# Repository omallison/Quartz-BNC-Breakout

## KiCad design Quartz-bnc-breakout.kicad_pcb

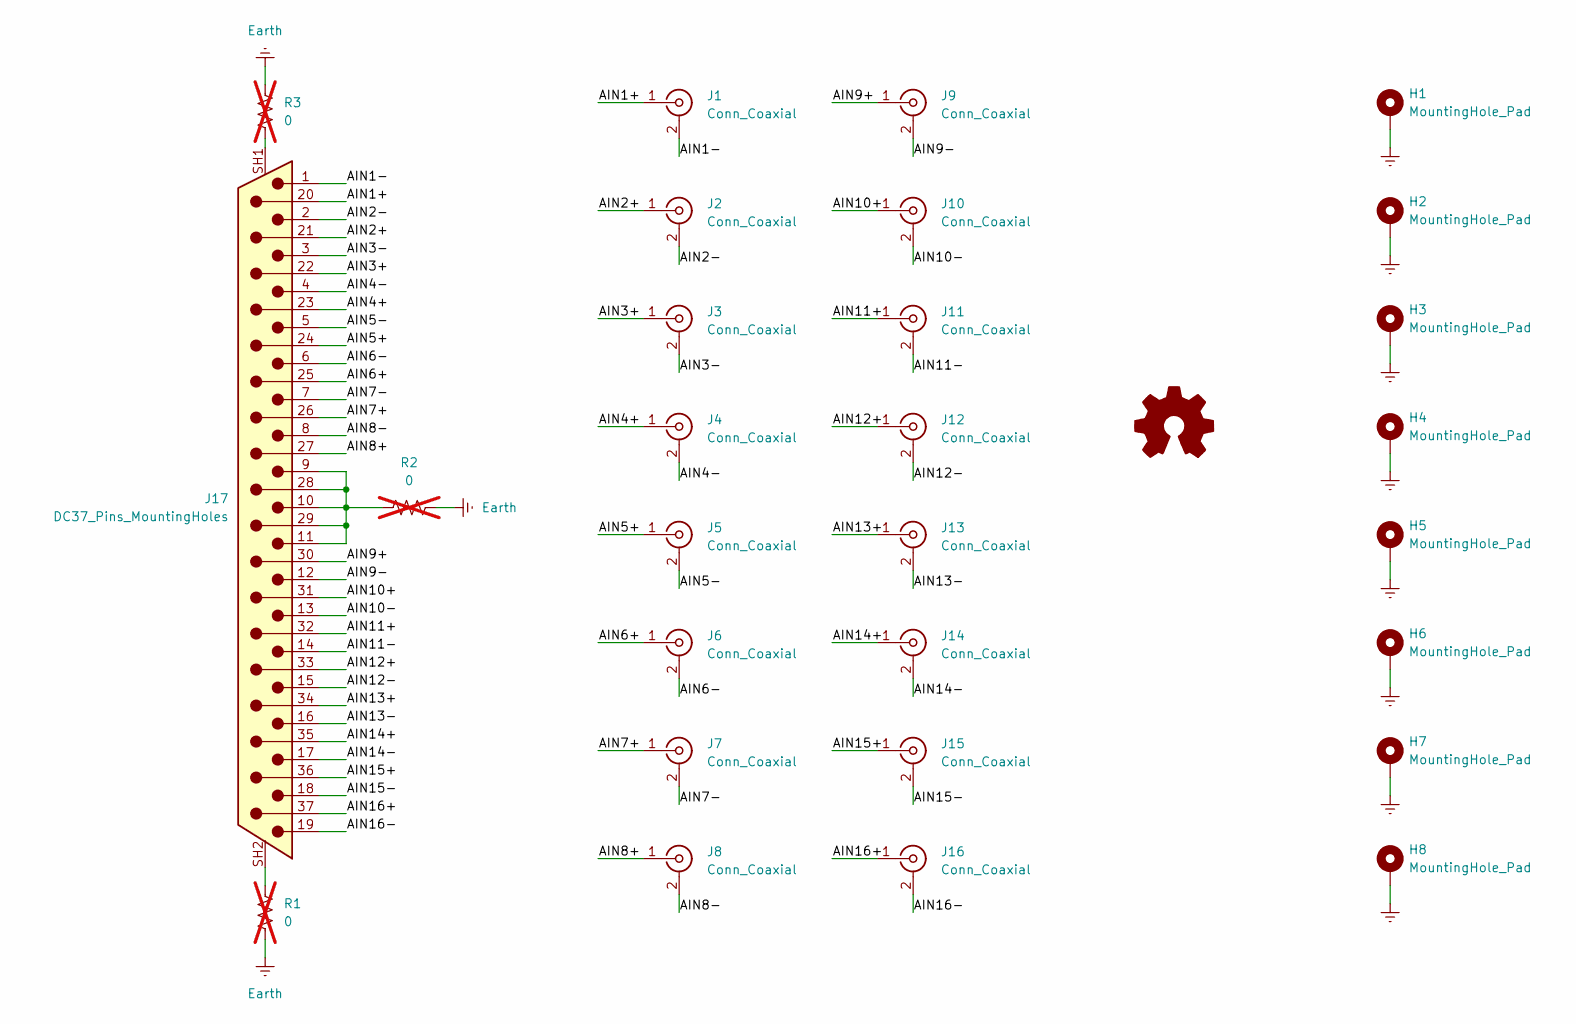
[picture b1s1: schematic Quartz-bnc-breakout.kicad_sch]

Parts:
H1, H2, H3, H4, H5, H6, H7, H8: MountingHole_Pad; MountingHole_3.4mm_Pad
J1, J2, J3, J4, J5, J6, J7, J8, J9, J10, J11, J12, J13, J14, J15, J16: Conn_Coaxial; BNC_Amphenol_031-5539_Vertical; MPN 5227222-2
J17: DC37_Pins_MountingHoles; DSUB-37_Pins_Vertical_P2.77x2.84mm_MountingHoles; MPN 5787686-1
Logo1: Logo_Open_Hardware_Small; Logo_2X
R1, R2, R3: 0; R_0805_2012Metric; not fitted

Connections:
/AIN1+: J1.1 (In), J17.20
/AIN1-: J1.2 (Ext), J17.1
/AIN2+: J2.1 (In), J17.21
/AIN2-: J2.2 (Ext), J17.2
/AIN3+: J3.1 (In), J17.22
/AIN3-: J3.2 (Ext), J17.3
/AIN4+: J4.1 (In), J17.23
/AIN4-: J4.2 (Ext), J17.4
/AIN5+: J5.1 (In), J17.24
/AIN5-: J5.2 (Ext), J17.5
/AIN6+: J6.1 (In), J17.25
/AIN6-: J6.2 (Ext), J17.6
/AIN7+: J7.1 (In), J17.26
/AIN7-: J7.2 (Ext), J17.7
/AIN8+: J8.1 (In), J17.27
/AIN8-: J8.2 (Ext), J17.8
/AIN9+: J9.1 (In), J17.30
/AIN9-: J9.2 (Ext), J17.12
/AIN10+: J10.1 (In), J17.31
/AIN10-: J10.2 (Ext), J17.13
/AIN11+: J11.1 (In), J17.32
/AIN11-: J11.2 (Ext), J17.14
/AIN12+: J12.1 (In), J17.33
/AIN12-: J12.2 (Ext), J17.15
/AIN13+: J13.1 (In), J17.34
/AIN13-: J13.2 (Ext), J17.16
/AIN14+: J14.1 (In), J17.35
/AIN14-: J14.2 (Ext), J17.17
/AIN15+: J15.1 (In), J17.36
/AIN15-: J15.2 (Ext), J17.18
/AIN16+: J16.1 (In), J17.37
/AIN16-: J16.2 (Ext), J17.19
Earth: H1.1, H2.1, H3.1, H4.1, H5.1, H6.1, H7.1, H8.1, R1.2, R2.2, R3.1
unnamed: J17.SH1 (PAD), R3.2
unnamed: J17.SH2 (PAD), R1.1
unnamed: J17.9, J17.10, J17.11, J17.28, J17.29, R2.1

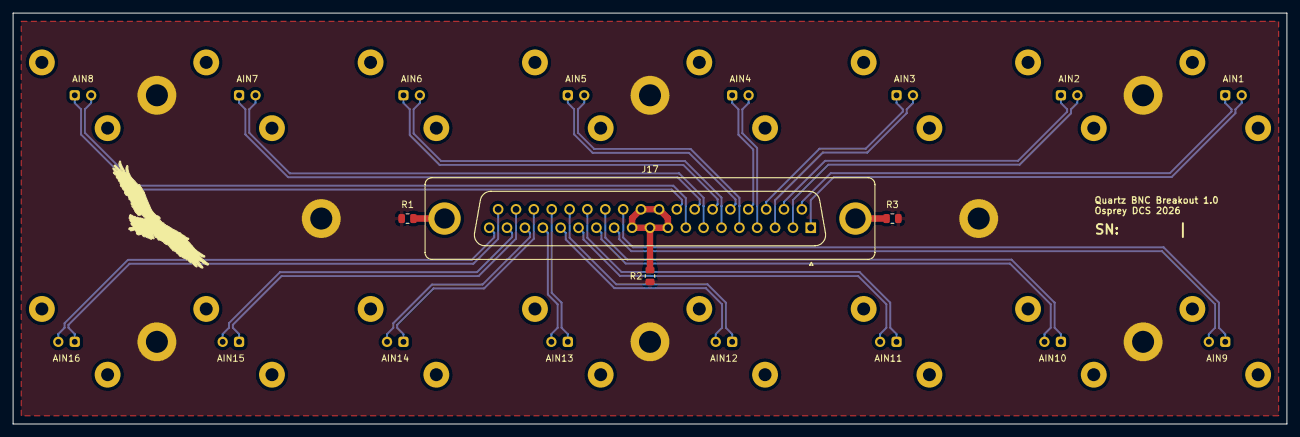
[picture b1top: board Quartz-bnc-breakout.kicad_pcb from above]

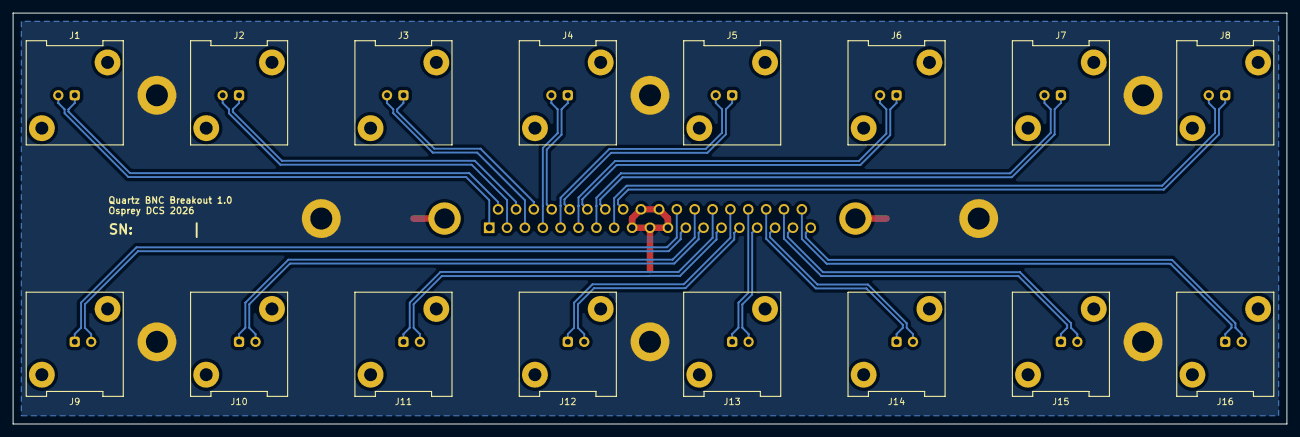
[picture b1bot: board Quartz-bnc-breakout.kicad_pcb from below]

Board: 2 copper layers, 196.8 x 63.5 mm, 29 parts (16 on the bottom side), 36 nets.

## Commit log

2026-05-28 Changed mounting hole footprints from 3mm to 3.4mm
2026-05-28 Added more padding to D mounting holes
2026-06-03 Updated correct D connector
2026-06-08 minor changes
